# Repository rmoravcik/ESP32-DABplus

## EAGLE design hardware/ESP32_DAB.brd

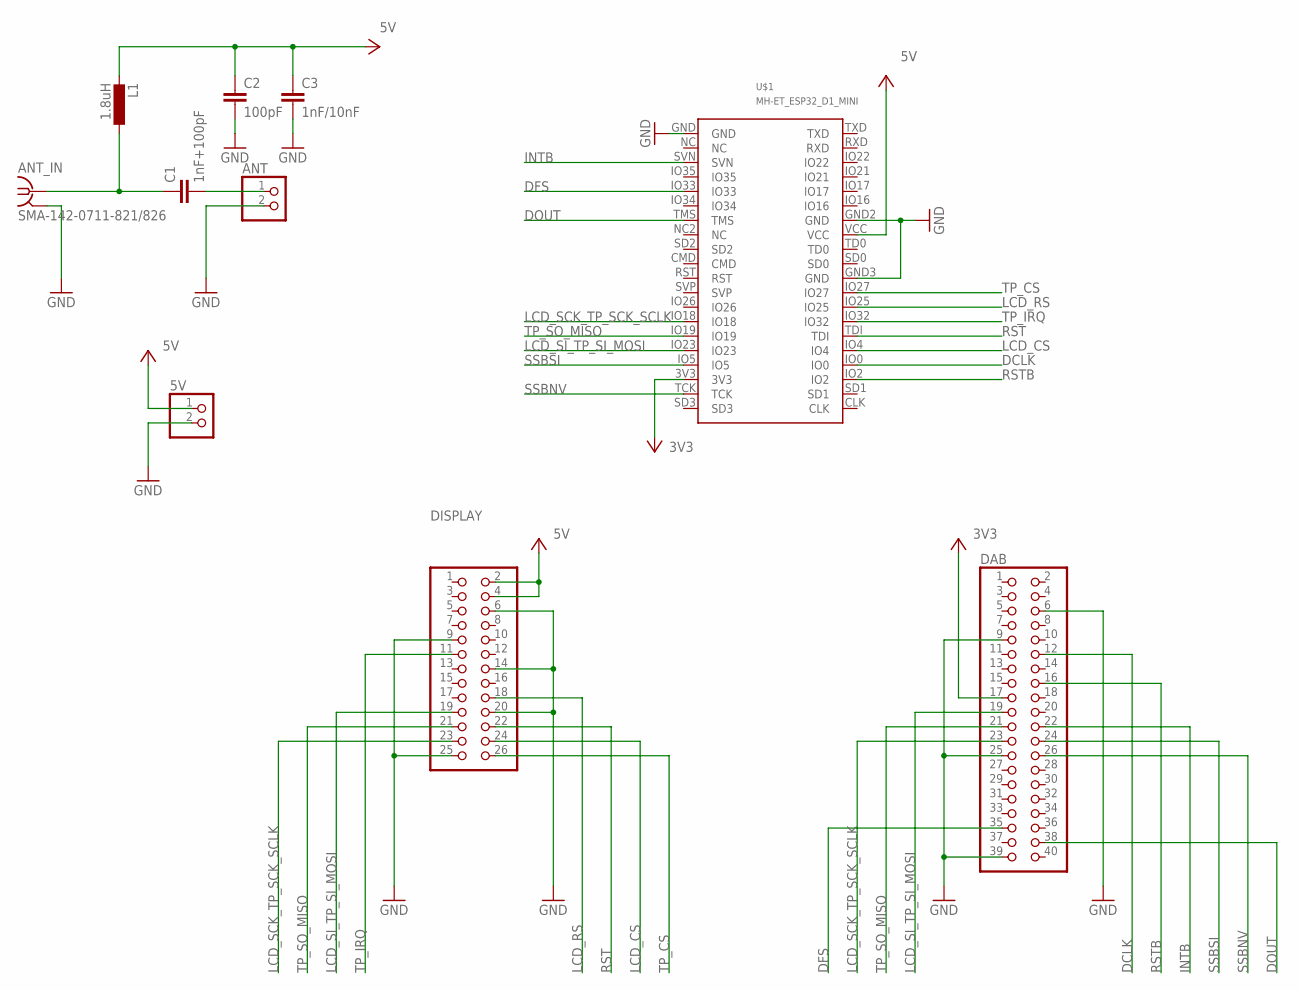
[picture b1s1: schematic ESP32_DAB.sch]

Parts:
5V: PINHD-1X2; 1X02
ANT: PINHD-1X2; 1X02
ANT_IN: SMA-142-0711-821/826; J502-ND-142-0711-821/826
C1: 1nF+100pF; C0805
C2: 100pF; C0805
C3: 1nF/10nF; C0805
DAB: PINHD-2X20; 2X20
DISPLAY: PINHD-2X13; 2X13
L1: 1.8uH; L1812
U$1: MH-ET_ESP32_D1_MINI

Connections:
3V3: DAB.17, U$1.3V3
5V: 5V.1, C2.1, C3.1, DISPLAY.2, DISPLAY.4, L1.2, U$1.VCC
DCLK: DAB.12, U$1.IO0
DFS: DAB.35, U$1.IO33
DOUT: DAB.38, U$1.TMS
GND: 5V.2, ANT.2, ANT_IN.G@1 (2), ANT_IN.G@2 (2), ANT_IN.G@3 (2), ANT_IN.G@4 (2), C2.2, C3.2, DAB.6, DAB.9, DAB.25, DAB.39, DISPLAY.6, DISPLAY.9, DISPLAY.14, DISPLAY.20, DISPLAY.25, U$1.GND, U$1.GND2 (GND), U$1.GND3 (GND)
INTB: DAB.22, U$1.SVN
LCD_CS: DISPLAY.24, U$1.IO4
LCD_RS: DISPLAY.18, U$1.IO25
LCD_SCK_TP_SCK_SCLK: DAB.23, DISPLAY.23, U$1.IO18
LCD_SI_TP_SI_MOSI: DAB.19, DISPLAY.19, U$1.IO23
unnamed: ANT_IN.1, C1.1, L1.1
unnamed: ANT.1, C1.2
RST: DISPLAY.22, U$1.TDI
RSTB: DAB.16, U$1.IO2
SSBNV: DAB.26, U$1.TCK
SSBSI: DAB.24, U$1.IO5
TP_CS: DISPLAY.26, U$1.IO27
TP_IRQ: DISPLAY.11, U$1.IO32
TP_SO_MISO: DAB.21, DISPLAY.21, U$1.IO19

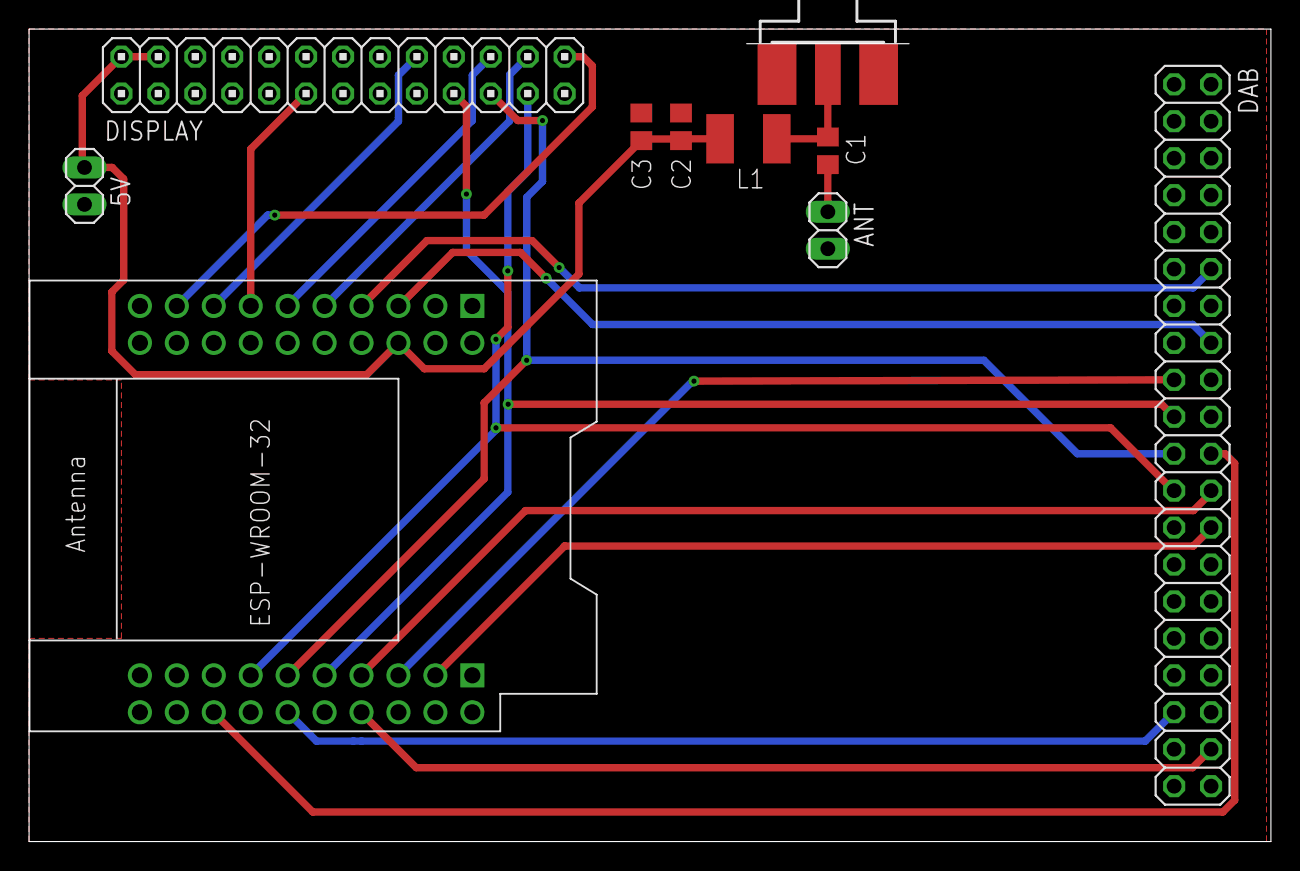
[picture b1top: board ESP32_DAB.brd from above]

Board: 2 copper layers, 85.4 x 55.9 mm, 10 parts (0 on the bottom side), 20 nets.

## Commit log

2025-03-04 Fixed RDS characters conversion. Added scrolling of shorter text
2025-03-05 Improved scanning and tunning
2025-03-05 Added loading and saving station list
2025-03-07 Fixed load and storing of station list
2025-03-09 Fixed crash and slideshow
2025-03-09 UTF8 converion of station label
2025-03-11 UI updates
2025-03-11 Faster tunning
2025-03-11 Improved calculation of signal quality
2025-03-23 Added main menu
2025-03-23 Added volume control
2025-03-23 Added scanning progress bar
2025-03-23 Speed up switching to scanning screen
2025-03-24 Added bluetooth menu
2025-03-30 Added connection to BT speaker, but crashing
2025-03-31 Streaming over BT working
2025-12-28 Use PSRAM for slideshow
2025-12-29 Added BT inidicator
2025-12-30 Improved volume control
2025-12-30 Added Bluetooth menu entries
2025-12-30 Added radio menu
2025-12-30 Bluetooth list working
2025-12-30 Fixed to disconnection
2025-12-31 Added station list
2025-12-31 Ignore some weird SSID causing crash
2025-12-31 Select page with selected entry
2025-12-31 Added update of status bar when menu is displayed
2025-12-31 Free some heap
2025-12-31 Save more heap
2026-01-24 Added schematics
2026-01-24 Fixed scrollbar position and show version during start
2026-01-24 Try to connect to last connected station
